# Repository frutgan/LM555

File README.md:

<h1> Diseño de placa básica con KICAD </h1>

<h3> Diseño de PCB para el encendido intermitente de un led mediante un LM555, incluyendo regulador de Tensión. </h3>

<dl>

<dt> Componentes a comprar: </dt>
<dd> 
<li type="circle">	Led rojo </li>
<li type="circle">	1 Resistencia de 300 Ohmios </li>
<li type="circle">  1 Resistencia de 120 Ohmios </li>
<li type="circle">	1 Resistencia de 10k Ohmios </li>
<li type="circle">	1 BARREL_Jack </li>
<li type="circle">  1 LM555 </li>
<li type="circle">	1 LM7805 </li>
<li type="circle">	1 Terminal Block connector</li>

</dd>
</d1>

<h4> Tenéis fotos del resultado de la placa en el repositorio</h4>

<p> Especial agradecimiento a los tutoriales de "TUTOELECTRO" & "RINCÓN INGENIERIL" </p>

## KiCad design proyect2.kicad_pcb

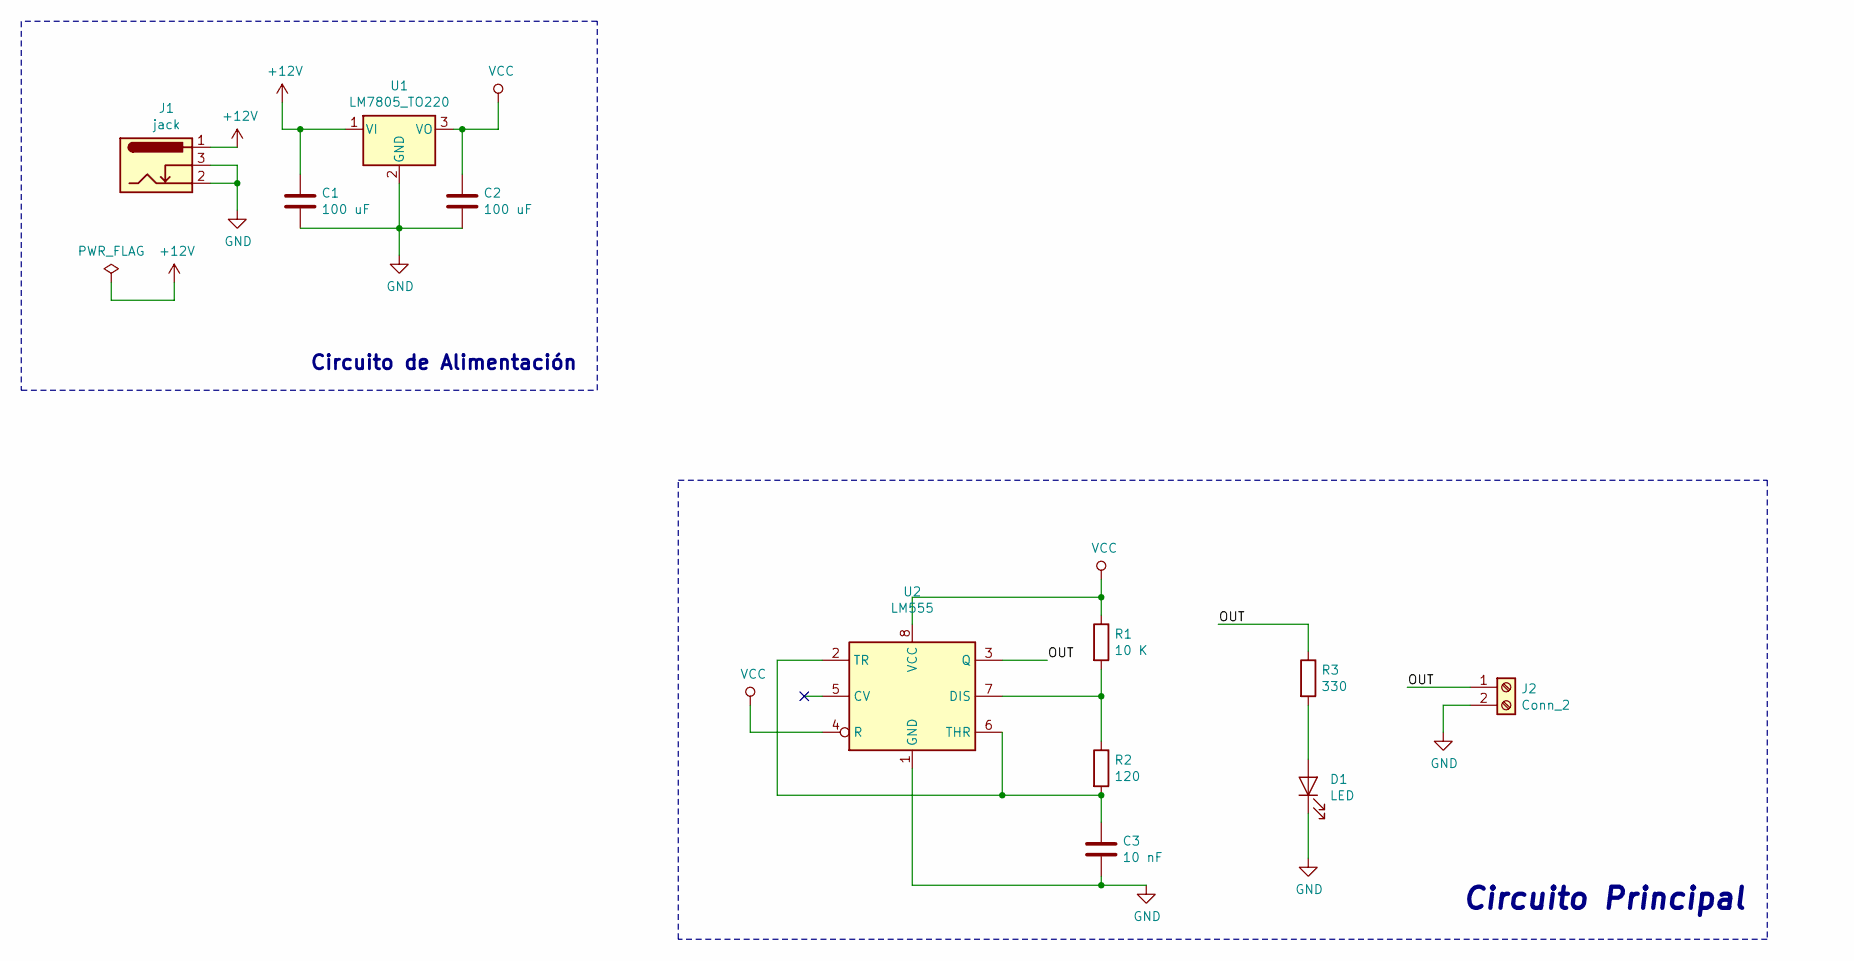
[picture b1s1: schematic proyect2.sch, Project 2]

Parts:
C1, C2: 100 uF; C_Disc_D3.0mm_W1.6mm_P2.50mm
C3: 10 nF; C_Disc_D3.4mm_W2.1mm_P2.50mm
D1: LED; LED_D3.0mm
J1: jack; BarrelJack_Horizontal
J2: Conn_2; TerminalBlock_bornier-2_P5.08mm
R1: 10 K; R_Axial_DIN0204_L3.6mm_D1.6mm_P1.90mm_Vertical
R2: 120; R_Axial_DIN0204_L3.6mm_D1.6mm_P1.90mm_Vertical
R3: 330; R_Axial_DIN0204_L3.6mm_D1.6mm_P1.90mm_Vertical
U1: LM7805_TO220; TO-220-3_Vertical
U2: LM555; DIP-8_W7.62mm

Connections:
+12V: C1.1, J1.1, U1.1 (VI)
/OUT: J2.1, R3.1, U2.3 (Q)
GND: C1.2, C2.2, C3.2, D1.1 (K), J1.2, J1.3, J2.2, U1.2 (GND), U2.1 (GND)
unnamed: C3.1, R2.2, U2.2 (TR), U2.6 (THR)
unnamed: D1.2 (A), R3.2
unnamed: R1.2, R2.1, U2.7 (DIS)
VCC: C2.1, R1.1, U1.3 (VO), U2.4 (R), U2.8 (VCC)

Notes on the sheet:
Circuito de Alimentación
Circuito Principal

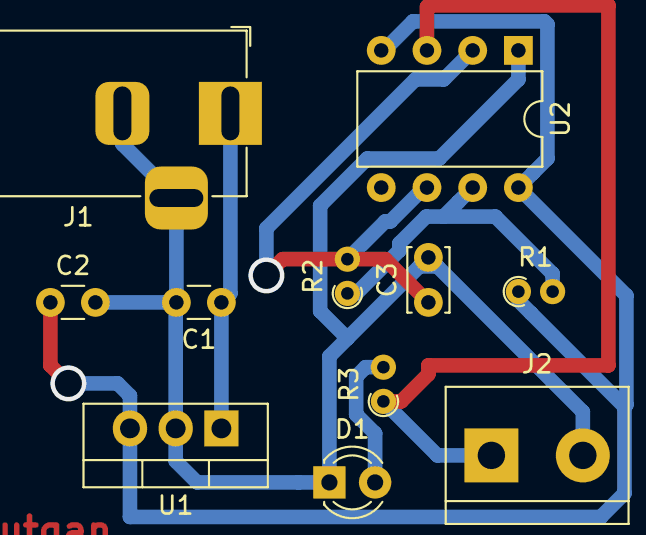
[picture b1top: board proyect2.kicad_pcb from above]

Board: 2 copper layers, 11 parts (0 on the bottom side), 7 nets.

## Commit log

2019-06-26 Subida de archivos
2019-06-26 Modificación
2019-06-26 mod2
